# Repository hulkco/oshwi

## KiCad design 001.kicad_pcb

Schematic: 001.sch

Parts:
C1: 100nF; C_0805_HandSoldering
C2, C4: 10nF; C_0805_HandSoldering
C3: 100uF; C_0805_HandSoldering
D1: DIODE-SCHOTTKY-40V-1A-MBRA140-SMA; D_SOD-123
D2: RED; LED_1206
J1: CONN_01X02; JST_PH_S2B-PH-SM4-TB_02x2.00mm_Angled
J2, J3, J4, J5, J6, J7, J8, J9, J10, J11, J12, J13, J14, J15, J16: TEST_1P; CONN-HEADER-STRAIGHT-P2.54MM-1x01
LED1, LED2, LED3, LED4, LED5: LED-RGB-WS2812B-4SMD; LED-RGB-5050-SMD
R1, R3, R4, R5, R6, R7: 10k; R_0805_HandSoldering
R2: 1k; R_0805_HandSoldering
SW1: USER/PROG; SW_SPST_KMR2
SW2: RESET; SW_SPST_KMR2
U1: ESP-12; ESP-12S_SMD
U2: SPX3819M5-L-1-8; SOT-23-5_HandSoldering

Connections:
+3.3V: C2.1, C3.1, C4.1, LED1.3 (VCC), LED2.3 (VCC), LED3.3 (VCC), LED4.3 (VCC), LED5.3 (VCC), R1.1, R2.1, R3.1, R4.1, R7.1, U1.8 (VCC), U2.5 (VOUT)
ADC: J4.1, U1.2 (ADC)
CH_PD: J6.1, R4.2, U1.3 (CH_PD)
GND: C1.2, C2.2, C3.2, C4.2, D2.1 (K), J1.2, J16.1, LED1.1 (GND), LED2.1 (GND), LED3.1 (GND), LED4.1 (GND), LED5.1 (GND), R6.1, SW1.1, SW1.2, SW2.1, SW2.2, U1.9 (GND), U2.2 (GND)
GPIO0: J11.1, R3.2, SW1.3, SW1.4, U1.12 (GPIO0)
GPIO2: J9.1, R7.2, U1.11 (GPIO2)
GPIO4: LED1.2 (DI), U1.13 (GPIO4)
GPIO5: J7.1, U1.14 (GPIO5)
GPIO12: J10.1, U1.6 (GPIO12)
GPIO13: J12.1, U1.7 (GPIO13)
GPIO14: J8.1, U1.5 (GPIO14)
GPIO15: J13.1, R6.2, U1.10 (GPIO15)
GPIO16: J14.1, U1.4 (GPIO16)
unnamed: D2.2 (A), R2.2
unnamed: LED1.4 (DO), LED2.2 (DI)
unnamed: LED2.4 (DO), LED3.2 (DI)
unnamed: LED3.4 (DO), LED4.2 (DI)
unnamed: LED4.4 (DO), LED5.2 (DI)
unnamed: R5.2, U2.3 (EN)
REST: J2.1, R1.2, SW2.3, SW2.4, U1.1 (REST)
RXD: J5.1, U1.15 (RXD)
TXD: J3.1, U1.16 (TXD)
VBAT: D1.2 (A), J1.1
VCC: C1.1, D1.1 (K), J15.1, R5.1, U2.1 (VIN)

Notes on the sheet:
POWER & FILTERING
ESP8266 MODULE
NEOPIXELS
BUTTONS & LED

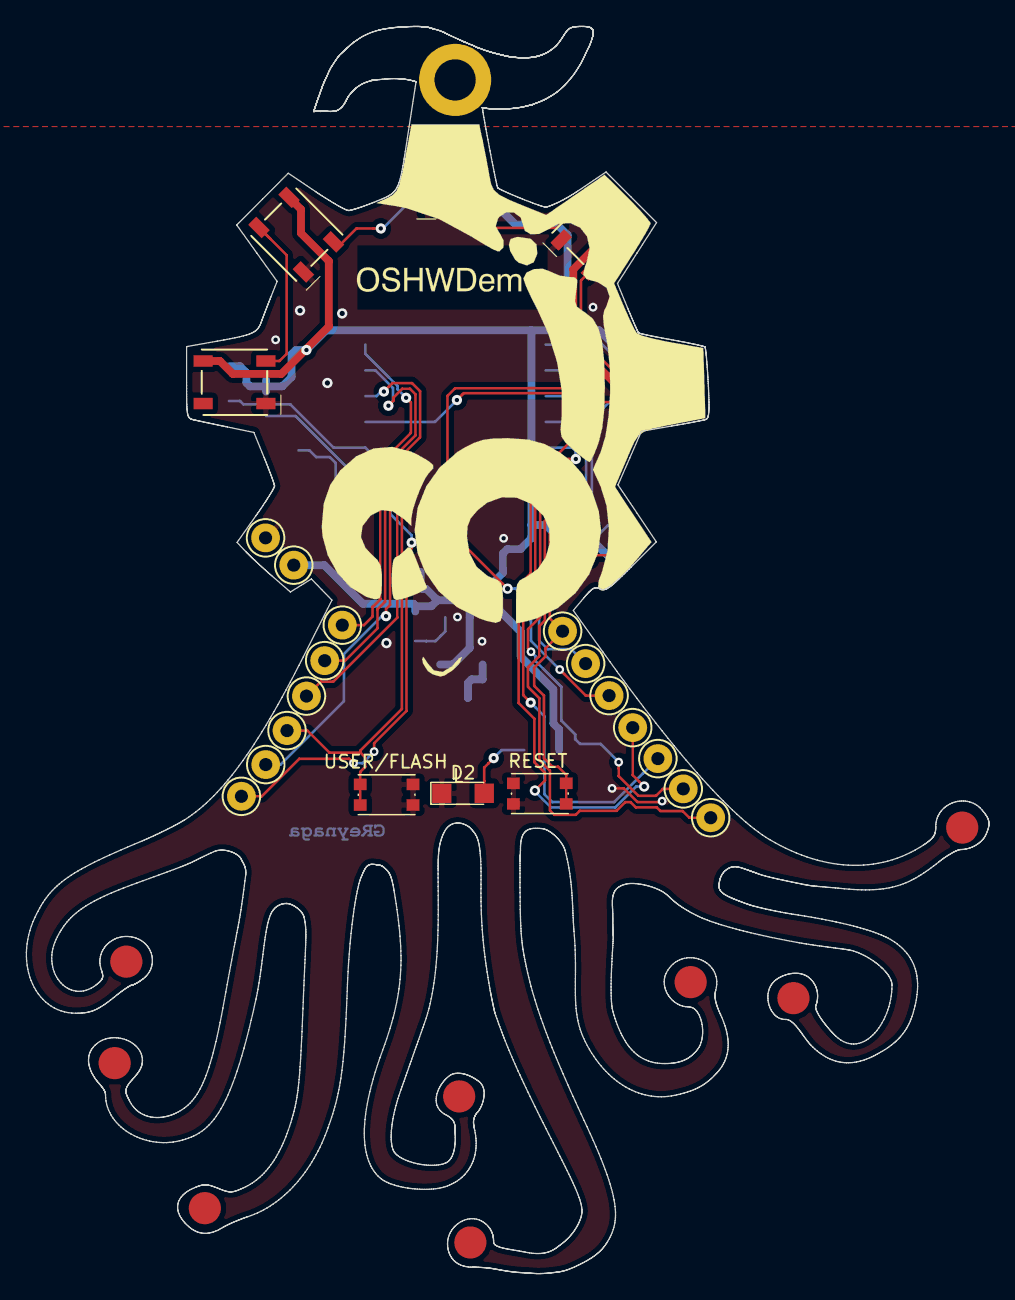
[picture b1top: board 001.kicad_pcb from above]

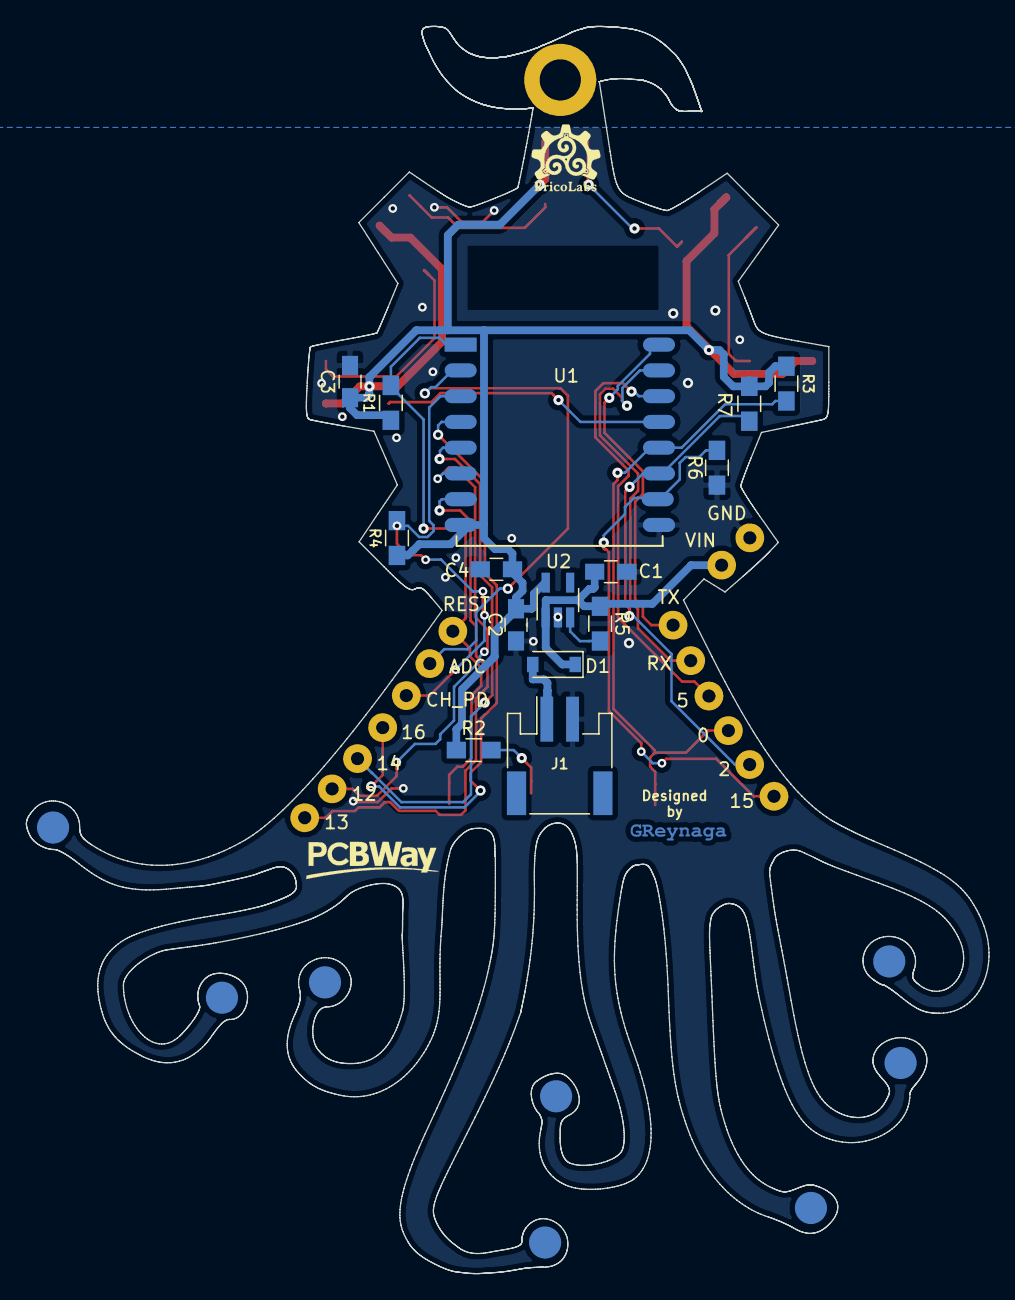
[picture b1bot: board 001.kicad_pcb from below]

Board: 2 copper layers, 74.7 x 96.8 mm, 61 parts (19 on the bottom side), 24 nets.

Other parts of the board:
BricoLabs-14***: LOGO; bricolabs-14
Eyes***: LOGO; Oshwdem_Eyes_08
GBSilk***: LOGO; greynaga6-2
GS***: v; greynaga6-2-cooper
Head***: LOGO; Oshwdem_Head_01
Mouth***: LOGO; Oshwdem_Mouth_01
PCBway-3: LOGO; pcbway3
REF1**, REF2**, REF3**, REF4**, REF5**, REF6**, REF7**, REF8**, REF9**, REF10**, REF11**, REF12**, REF13**, REF14**, REF15**, REF16**: PADS

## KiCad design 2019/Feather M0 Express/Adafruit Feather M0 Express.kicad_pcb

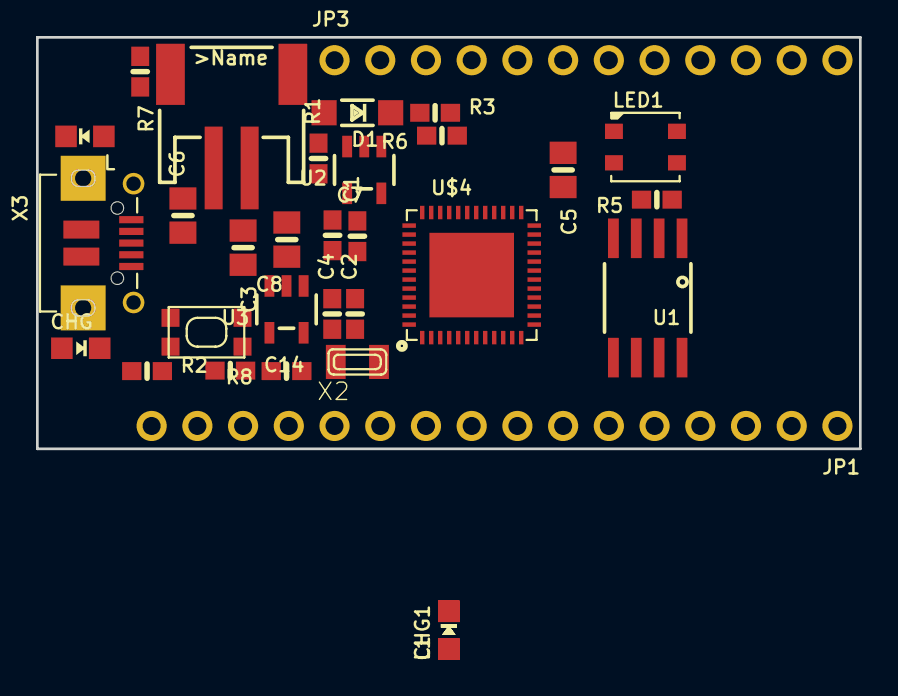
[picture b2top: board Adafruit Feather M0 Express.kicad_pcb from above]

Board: 2 copper layers, 45.7 x 22.9 mm, 34 parts (0 on the bottom side), 4 nets, no tracks yet.

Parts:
C1, C7, C14: 1uF; 0603-NO
C2, C4: 22pF; 0603-NO
C3, C6, C8: 10µF; 0805-NO
C5: 10uF; 0805-NO
CHG, CHG1: ORANGE; CHIPLED_0805_NOOUTLINE
D1: MBR120; SOD-123
JP1: HEADER-1X16ROUND; 1X16_ROUND
JP3: HEADER-1X12; 1X12_ROUND
L, L1: RED; CHIPLED_0805_NOOUTLINE
LED1: WS2812B3535; LED3535
R1, R3: 100k; 0603-NO
R2: 1K; 0603-NO
R5: 10K; 0603-NO
R6: 100K; 0603-NO
R7: 2.2K; 0603-NO
R8: 10K\; 0603-NO
SW1: SPST_TACT-KMR2; KMR2
TP1, TP2: TESTPOINTROUND1.5MM; TESTPOINT_ROUND_1.5MM
U1: 2MB Flash; SOIC8_208MIL
U2: AP2112-3.3; SOT23-5
U3: MCP73831T-2ACI/OT; SOT23-5
U$4: ATSAMD21G18_QFN; TQFN48_7MM
X1: JSTPH; JSTPH2
X2: 32.768; XTAL3215
X3: microUSB; 4UCONN_20329_V2

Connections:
GND: L.C, L1.C
unnamed: CHG.C, CHG1.C
unnamed: L.A, L1.A
VBUS: CHG.A, CHG1.A

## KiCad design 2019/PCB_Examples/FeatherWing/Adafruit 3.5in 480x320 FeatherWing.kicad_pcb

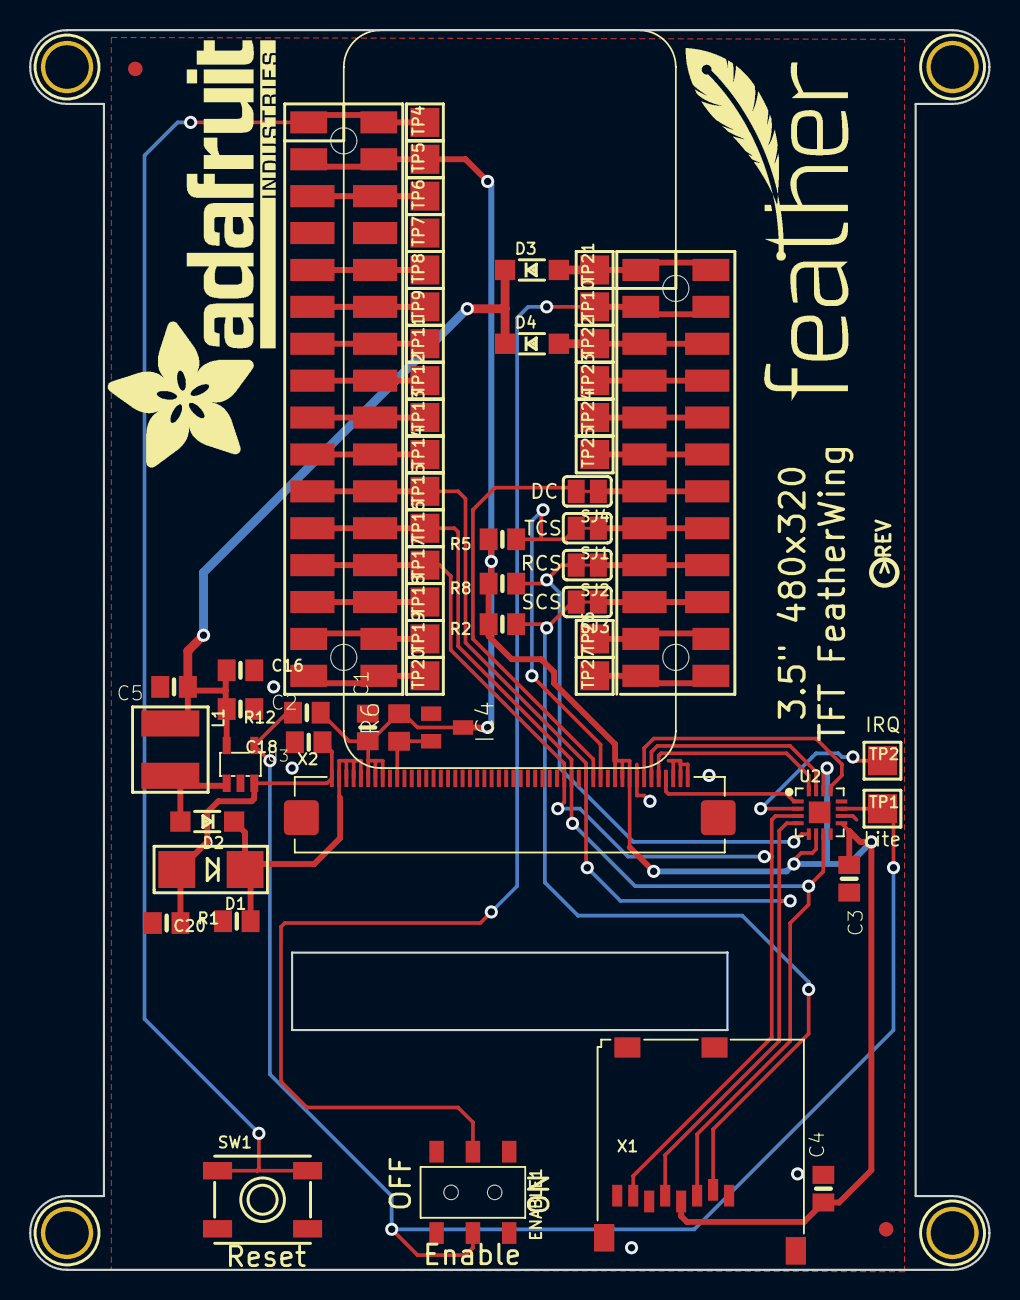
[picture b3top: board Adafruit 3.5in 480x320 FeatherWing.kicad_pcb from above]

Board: 16 copper layers, 66.0 x 85.3 mm, 66 parts (0 on the bottom side), 43 nets.

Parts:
C1, C16, C20: 1uF; 0805-NO
C2, C3, C4, C5: 10uF; 0805-NO
C18: 0.1uF; 0805-NO
D1: MM3Z24VT1G; SMADIODE
D2: MBR0540; SOD-123
D3, D4: MBR120; SOD-123
ENABLE1: Slide Switch; EG1390
IC4: APX803-SAG; SOT23
L1: 15uH; INDUCTOR_5X5MM_NR5040_NOTHERMALS
MS2: FEATHERWING_SMTDUAL; FEATHERWING_SMT2
R1: 12Ω; 0805-NO
R2, R5, R8: 100K; 0805-NO
R6: 10K; R0805
R12: 10K; 0805-NO
SJ1, SJ2, SJ3, SJ4: SOLDERJUMPER_CLOSED; SOLDERJUMPER_CLOSEDWIRE
SW1: EVQQ2; EVQ-Q2_SMALLER
TP1, TP2, TP4, TP5, TP6, TP7, TP8, TP9, TP10, TP11, TP12, TP13, TP14, TP15, TP16, TP17, TP18, TP19, TP20, TP21, TP22, TP23, TP24, TP25, TP26, TP27: TESTPOINTPAD2MM; TESTPOINT_PAD_2MM
U2: STMPE811; QFN16_3MM
U3: FAN5333BSX; SOT23-5@1
U$7, U$15, U$16, U$17: MOUNTINGHOLE3.0THIN; MOUNTINGHOLE_3.0_PLATEDTHIN
U$9, U$23: FIDUCIAL_1MM
U$11: FEATHERLOGO
U$19: ADAFRUIT_TEXT_30MM
U$37: PCBFEAT-REV-040
X1: MicroSD; MICROSD
X2: 3.5" TFT; TFT_3.5IN_320X480_50PIN

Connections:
3.3V: C1.1, C3.1, C4.1, IC4.3, MS2.2, MS2.2', R2.2, R5.2, R6.2, R8.2, R12.1, TP5.P$1, U2.6, U2.9, U2.14, X1.4, X2.6, X2.7, X2.8, X2.40, X2.41, X2.42
+5V: C2.1, C5.1, C16.1, D3.C, D4.C, L1.P$1, U3.5
+24V: C20.1, D1.C, D2.C, X2.2, X2.3, X2.4, X2.5
/EN: ENABLE1.P2, MS2.27, MS2.27', TP10.P$1
/LCD_LITE: ENABLE1.P1, R12.2, TP1.P$1, U2.11, U3.4
/LEDK: C18.1, D1.A, R1.2, U3.3, X2.1
/MISO: MS2.13, MS2.13', TP17.P$1, U2.3, X1.7, X2.33
/MOSI: MS2.12, MS2.12', TP16.P$1, U2.7, X1.3, X2.34
/RT_CS: R8.1, SJ2.2, U2.5
/RT_INT: TP2.P$1, U2.2
/SCLK: MS2.11, MS2.11', TP15.P$1, U2.4, X1.5, X2.36
/SD_CS: R2.1, SJ3.2, X1.2
/TFT_CS: R5.1, SJ1.2, X2.38
/TFT_DC: SJ4.2, X2.37
/XL: U2.16, X2.46
/XR: U2.13, X2.44
/YD: U2.15, X2.45
/YU: U2.1, X2.47
/~TFT_RST: IC4.2, R6.1, X2.10
GND: C1.2, C2.2, C3.2, C4.2, C5.2, C16.2, C18.2, C20.2, ENABLE1.S1, ENABLE1.S2, IC4.1, MS2.4, MS2.4', R1.1, SW1.A, SW1.A', TP7.P$1, U2.10, U3.2, X1.6, X1.MT1, X1.MT2, X2.43, X2.48, X2.49, X2.50
unnamed: D2.A, L1.P$2, U3.1
unnamed: D3.A, MS2.28, MS2.28', TP21.P$1
unnamed: D4.A, MS2.26, MS2.26', TP22.P$1
unnamed: MS2.1, MS2.1', SW1.B, SW1.B', TP4.P$1
unnamed: MS2.3, MS2.3', TP6.P$1
unnamed: MS2.5, MS2.5', TP8.P$1
unnamed: MS2.6, MS2.6', TP9.P$1
unnamed: MS2.7, MS2.7', TP11.P$1
unnamed: MS2.8, MS2.8', TP12.P$1
unnamed: MS2.9, MS2.9', TP13.P$1
unnamed: MS2.10, MS2.10', TP14.P$1
unnamed: MS2.14, MS2.14', TP18.P$1
unnamed: MS2.15, MS2.15', TP19.P$1
unnamed: MS2.16, MS2.16', TP20.P$1
unnamed: MS2.17, MS2.17', TP27.P$1
unnamed: MS2.18, MS2.18', TP26.P$1
unnamed: MS2.19, MS2.19', SJ3.1
unnamed: MS2.20, MS2.20', SJ2.1
unnamed: MS2.21, MS2.21', SJ1.1
unnamed: MS2.22, MS2.22', SJ4.1
unnamed: MS2.23, MS2.23', TP25.P$1
unnamed: MS2.24, MS2.24', TP24.P$1
unnamed: MS2.25, MS2.25', TP23.P$1
